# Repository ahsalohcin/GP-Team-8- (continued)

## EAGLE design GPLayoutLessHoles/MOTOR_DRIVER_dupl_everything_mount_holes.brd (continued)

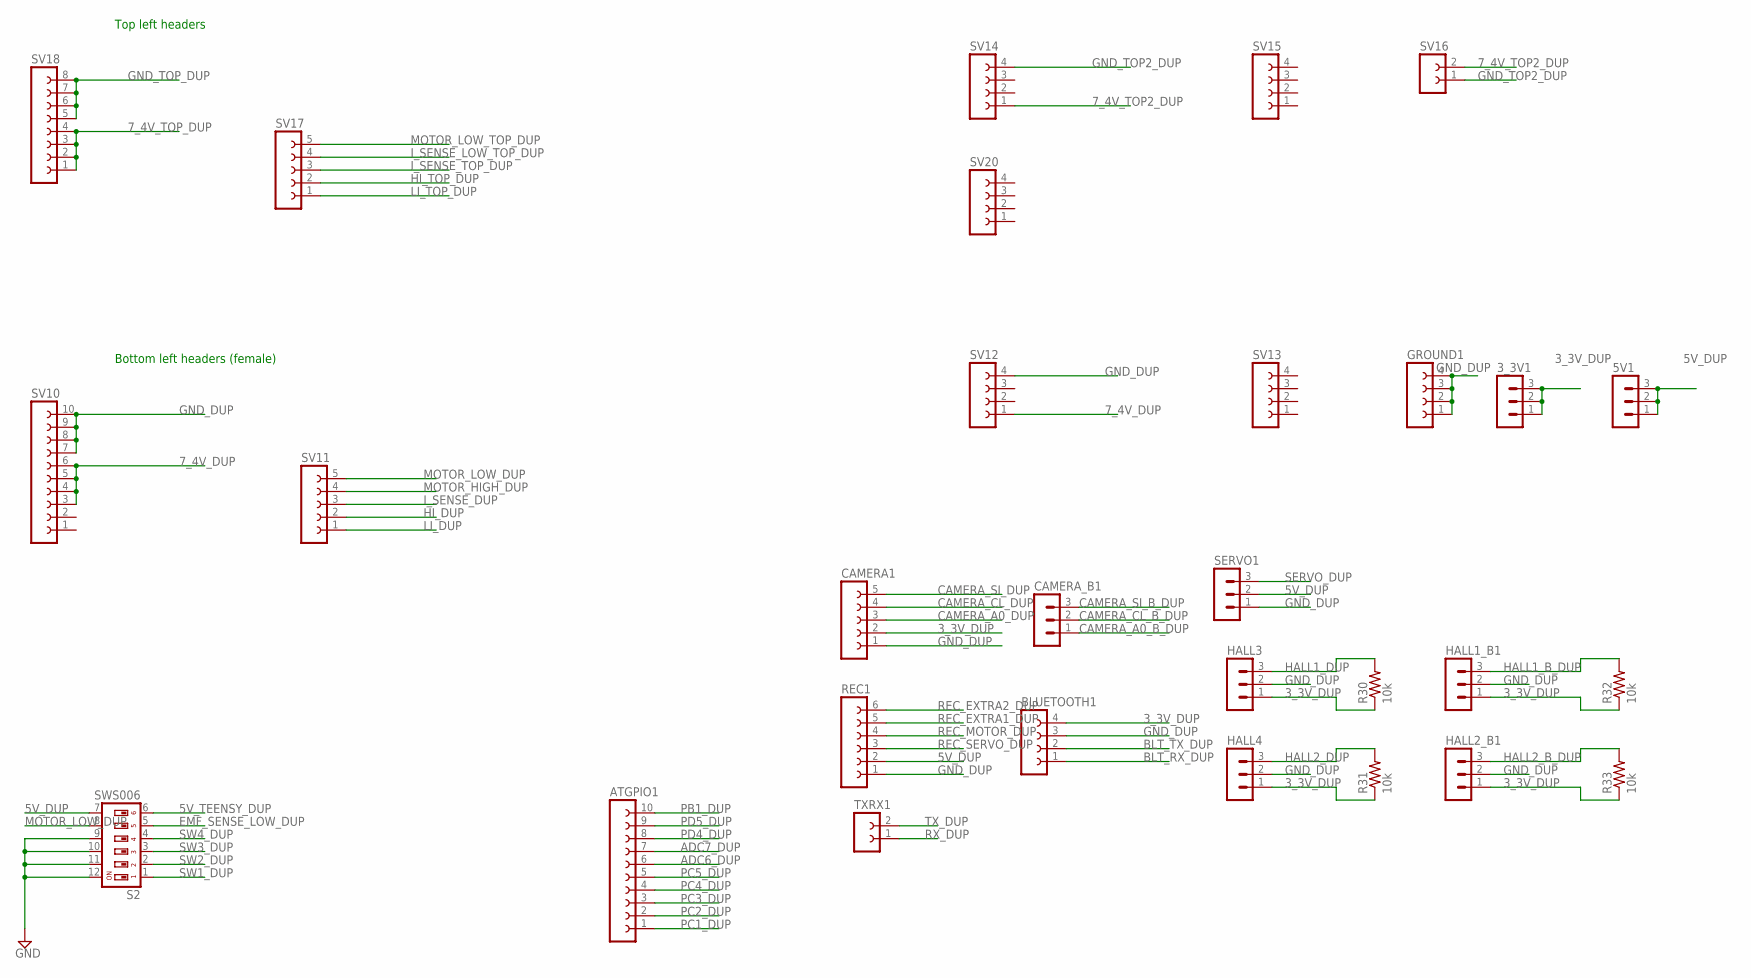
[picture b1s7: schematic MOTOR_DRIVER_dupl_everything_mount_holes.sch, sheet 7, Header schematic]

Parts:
3_3V1, 5V1: MA03-1
ATGPIO1: FE10-1; FE10
BLUETOOTH1: FE04-1; MANUFACTURER_PART_NUMBER HC-06
CAMERA1: FE05-1; MANUFACTURER_PART_NUMBER 28317; DIGIKEY_PART_NUMBER 28317-ND
CAMERA_B1: MA03-1; MANUFACTURER_PART_NUMBER 28317; DIGIKEY_PART_NUMBER 28317-ND
GROUND1: FE04-1
HALL1_B1, HALL2_B1, HALL3, HALL4: MA03-1; MANUFACTURER_PART_NUMBER US1881LUA-AAA-000-BU; DIGIKEY_PART_NUMBER US1881LUA-AAA-000-BU-ND
R30, R31, R32, R33: 10k; R0603
REC1: FE06-1; FE06
S2: SWS006; SMS-006; MANUFACTURER_PART_NUMBER 219-6MST; DIGIKEY_PART_NUMBER CT2196MST-ND
SERVO1: MA03-1; MANUFACTURER_PART_NUMBER TS-P12S
SV10: FE10-1; FE10
SV11, SV17: FE05-1
SV12, SV13, SV14, SV15, SV20: FE04-1
SV16: FE02-1
SV18: FE08-1; FE08
TXRX1: FE02-1

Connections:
3_3V_DUP: 3_3V1.1, 3_3V1.2, 3_3V1.3, BLUETOOTH1.4, CAMERA1.2, HALL1_B1.1, HALL2_B1.1, HALL3.1, HALL4.1, R30.1, R31.1, R32.1, R33.1; also elsewhere on the board
5V_DUP: 5V1.1, 5V1.2, 5V1.3, REC1.2, S2.7, SERVO1.2; also elsewhere on the board
5V_TEENSY_DUP: S2.6; also elsewhere on the board
7_4V_DUP: SV10.3, SV10.4, SV10.5, SV10.6, SV12.1; also elsewhere on the board
7_4V_TOP2_DUP: SV14.1, SV16.2; also elsewhere on the board
7_4V_TOP_DUP: SV18.1, SV18.2, SV18.3, SV18.4; also elsewhere on the board
ADC6_DUP: ATGPIO1.6; also elsewhere on the board
ADC7_DUP: ATGPIO1.7; also elsewhere on the board
BLT_RX_DUP: BLUETOOTH1.1; also elsewhere on the board
BLT_TX_DUP: BLUETOOTH1.2; also elsewhere on the board
CAMERA_A0_B_DUP: CAMERA_B1.1; also elsewhere on the board
CAMERA_A0_DUP: CAMERA1.3; also elsewhere on the board
CAMERA_CL_B_DUP: CAMERA_B1.2; also elsewhere on the board
CAMERA_CL_DUP: CAMERA1.4; also elsewhere on the board
CAMERA_SI_B_DUP: CAMERA_B1.3; also elsewhere on the board
CAMERA_SI_DUP: CAMERA1.5; also elsewhere on the board
EMF_SENSE_LOW_DUP: S2.5; also elsewhere on the board
GND_DUP: BLUETOOTH1.3, CAMERA1.1, GROUND1.1, GROUND1.2, GROUND1.3, GROUND1.4, HALL1_B1.2, HALL2_B1.2, HALL3.2, HALL4.2, REC1.1, S2.9, S2.10, S2.11, S2.12, SERVO1.1, SV10.7, SV10.8, SV10.9, SV10.10, SV12.4; also elsewhere on the board
GND_TOP2_DUP: SV14.4, SV16.1; also elsewhere on the board
GND_TOP_DUP: SV18.5, SV18.6, SV18.7, SV18.8; also elsewhere on the board
HALL1_B_DUP: HALL1_B1.3, R32.2; also elsewhere on the board
HALL1_DUP: HALL3.3, R30.2; also elsewhere on the board
HALL2_B_DUP: HALL2_B1.3, R33.2; also elsewhere on the board
HALL2_DUP: HALL4.3, R31.2; also elsewhere on the board
HI_DUP: SV11.2; also elsewhere on the board
HI_TOP_DUP: SV17.2; also elsewhere on the board
I_SENSE_DUP: SV11.3; also elsewhere on the board
I_SENSE_LOW_TOP_DUP: SV17.4; also elsewhere on the board
I_SENSE_TOP_DUP: SV17.3; also elsewhere on the board
LI_DUP: SV11.1; also elsewhere on the board
LI_TOP_DUP: SV17.1; also elsewhere on the board
MOTOR_HIGH_DUP: SV11.4; also elsewhere on the board
MOTOR_LOW_DUP: S2.8, SV11.5; also elsewhere on the board
MOTOR_LOW_TOP_DUP: SV17.5; also elsewhere on the board
PB1_DUP: ATGPIO1.10; also elsewhere on the board
PC1_DUP: ATGPIO1.1; also elsewhere on the board
PC2_DUP: ATGPIO1.2; also elsewhere on the board
PC3_DUP: ATGPIO1.3; also elsewhere on the board
PC4_DUP: ATGPIO1.4; also elsewhere on the board
PC5_DUP: ATGPIO1.5; also elsewhere on the board
PD4_DUP: ATGPIO1.8; also elsewhere on the board
PD5_DUP: ATGPIO1.9; also elsewhere on the board
REC_EXTRA1_DUP: REC1.5; also elsewhere on the board
REC_EXTRA2_DUP: REC1.6; also elsewhere on the board
REC_MOTOR_DUP: REC1.4; also elsewhere on the board
REC_SERVO_DUP: REC1.3; also elsewhere on the board
RX_DUP: TXRX1.1; also elsewhere on the board
SERVO_DUP: SERVO1.3; also elsewhere on the board
SW1_DUP: S2.1; also elsewhere on the board
SW2_DUP: S2.2; also elsewhere on the board
SW3_DUP: S2.3; also elsewhere on the board
SW4_DUP: S2.4; also elsewhere on the board
TX_DUP: TXRX1.2; also elsewhere on the board

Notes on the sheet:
Bottom left headers (female)
Top left headers

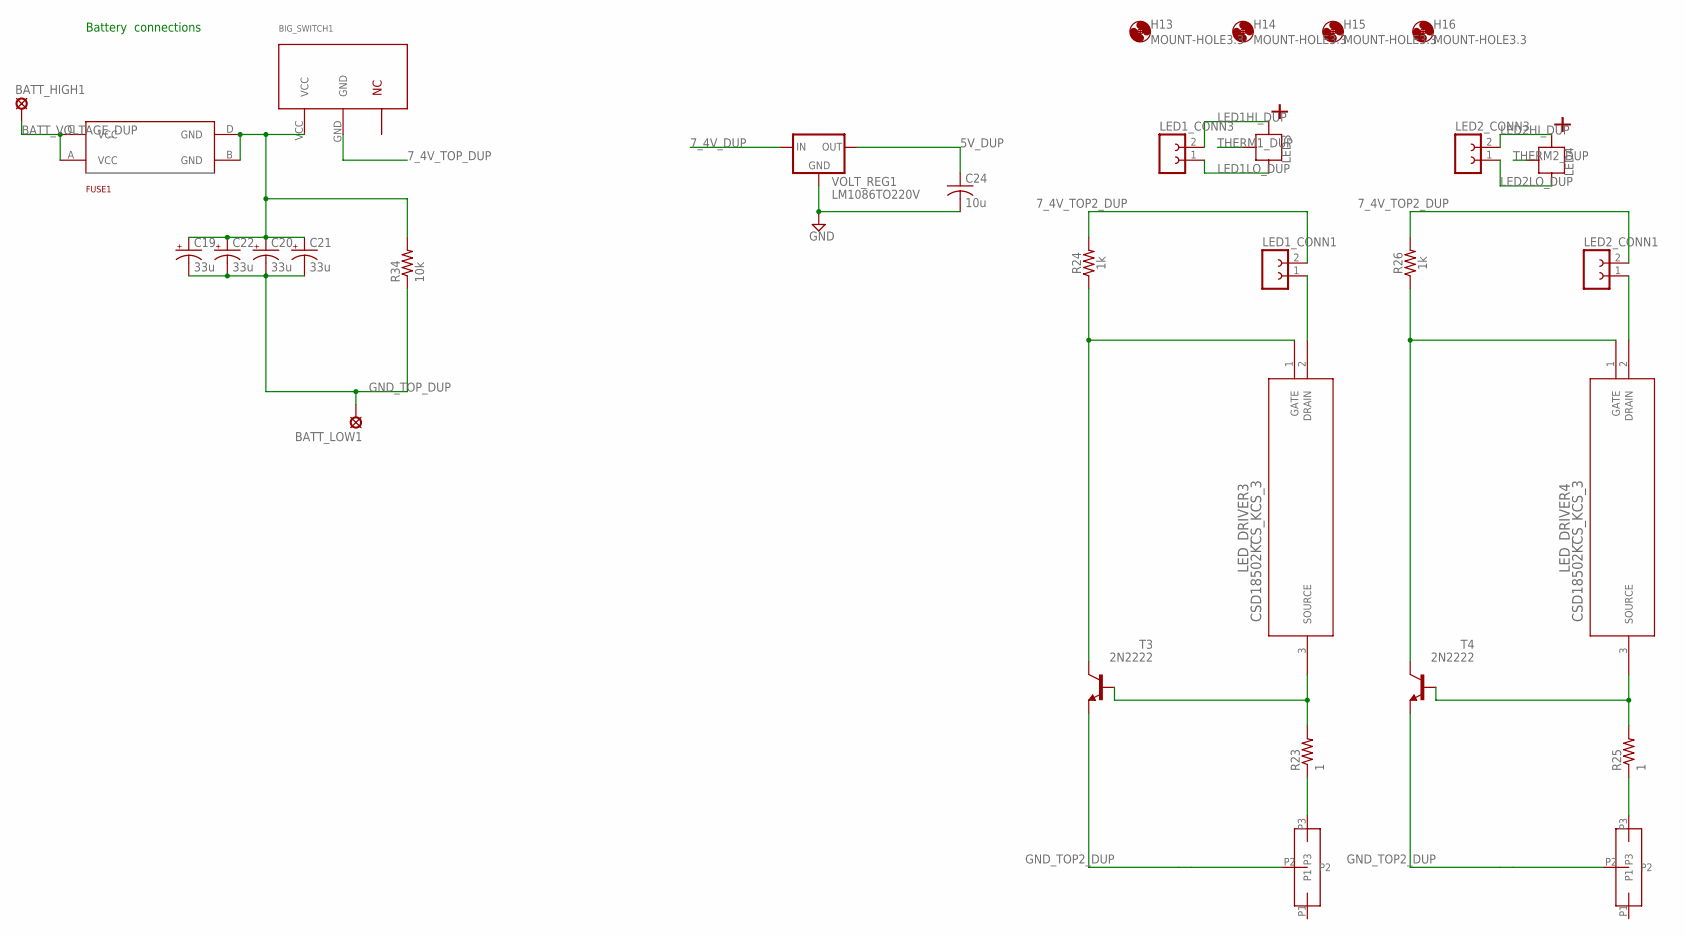
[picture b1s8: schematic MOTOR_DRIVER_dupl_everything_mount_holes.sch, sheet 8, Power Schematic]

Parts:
BATT_HIGH1: SE14
BATT_LOW1: SE14
BIG_SWITCH1: BIGSWITCH; MANUFACTURER_PART_NUMBER GRB238B801BR1; DIGIKEY_PART_NUMBER CW106-ND
C19, C20, C21, C22: 33u; 153CLV-1010
C24: 10u; C0805
FUSE1: FUSEHOLDER3588; MANUFACTURER_PART_NUMBER 0891010.NXS; DIGIKEY_PART_NUMBER F4989-ND
H13, H14, H15, H16: MOUNT-HOLE3.3; 3,3
LED1_CONN1, LED1_CONN3, LED2_CONN1, LED2_CONN3: FE02-1
LED3, LED4: CREE_XP; XP
LED_DRIVER3, LED_DRIVER4: CSD18502KCS_KCS_3; KCS3
R23, R25: 1; R2512
R24, R26: 1k; AXIAL-0.3
R34: 10k; R0603
T3, T4: 2N2222; TO18
U$14, U$15: POT
VOLT_REG1: LM1086TO220V; TO220S; MANUFACTURER_PART_NUMBER LM1086IT-5.0/NOPB; DIGIKEY_PART_NUMBER LM1086IT-5.0/NOPB-ND

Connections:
5V_DUP: C24.1, VOLT_REG1.2 (OUT); also elsewhere on the board
7_4V_DUP: VOLT_REG1.3 (IN); also elsewhere on the board
7_4V_TOP2_DUP: LED1_CONN1.2, LED2_CONN1.2, R24.P$2 (2), R26.P$2 (2); also elsewhere on the board
7_4V_TOP_DUP: BIG_SWITCH1.GND; also elsewhere on the board
BATT_VOLTAGE_DUP: BATT_HIGH1.MP, FUSE1.A (VCC), FUSE1.C (VCC)
GND_DUP: C24.2, VOLT_REG1.1 (GND); also elsewhere on the board
GND_TOP2_DUP: T3.1 (E), T4.1 (E), U$14.P2, U$15.P2; also elsewhere on the board
GND_TOP_DUP: BATT_LOW1.MP, C19.-, C20.-, C21.-, C22.-, R34.1; also elsewhere on the board
LED1HI_DUP: LED1_CONN3.2, LED3.POSITIVE, LED3.POSITIVE1 (POSITIVE)
LED1LO_DUP: LED1_CONN3.1, LED3.NEGATIVE, LED3.NEGATIVE1 (NEGATIVE)
LED2HI_DUP: LED2_CONN3.2, LED4.POSITIVE, LED4.POSITIVE1 (POSITIVE)
LED2LO_DUP: LED2_CONN3.1, LED4.NEGATIVE, LED4.NEGATIVE1 (NEGATIVE)
unnamed: BIG_SWITCH1.VCC, C19.+, C20.+, C21.+, C22.+, FUSE1.B (GND), FUSE1.D (GND), R34.2
unnamed: R23.1, U$14.P3
unnamed: LED_DRIVER3.3 (SOURCE), R23.2, T3.2 (B)
unnamed: LED_DRIVER3.1 (GATE), R24.P$1 (1), T3.3 (C)
unnamed: LED1_CONN1.1, LED_DRIVER3.2 (DRAIN)
unnamed: R25.1, U$15.P3
unnamed: LED_DRIVER4.3 (SOURCE), R25.2, T4.2 (B)
unnamed: LED_DRIVER4.1 (GATE), R26.P$1 (1), T4.3 (C)
unnamed: LED2_CONN1.1, LED_DRIVER4.2 (DRAIN)
THERM1_DUP: LED3.THERMAL
THERM2_DUP: LED4.THERMAL

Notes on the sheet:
Battery connections

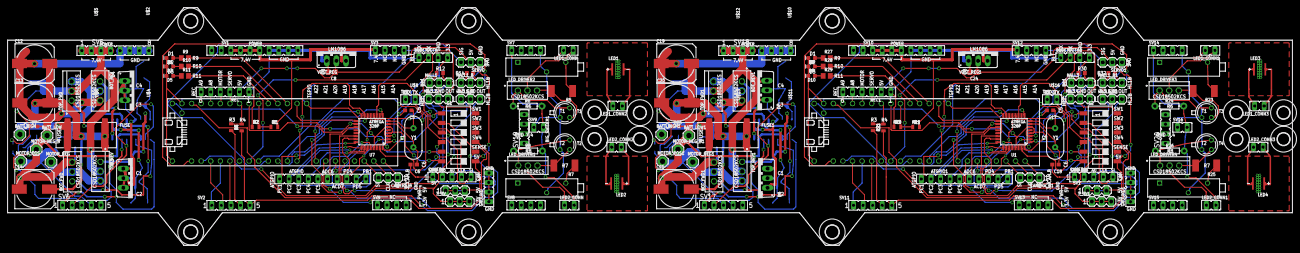
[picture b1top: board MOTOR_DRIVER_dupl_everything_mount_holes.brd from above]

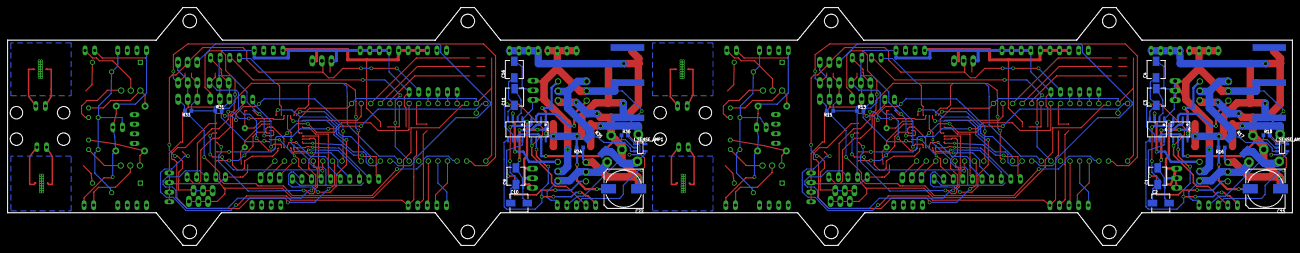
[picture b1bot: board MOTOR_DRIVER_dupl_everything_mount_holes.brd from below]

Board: 2 copper layers, 340.4 x 63.0 mm, 206 parts (26 on the bottom side), 180 nets.

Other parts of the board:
U$8, U$16: HEATSINK

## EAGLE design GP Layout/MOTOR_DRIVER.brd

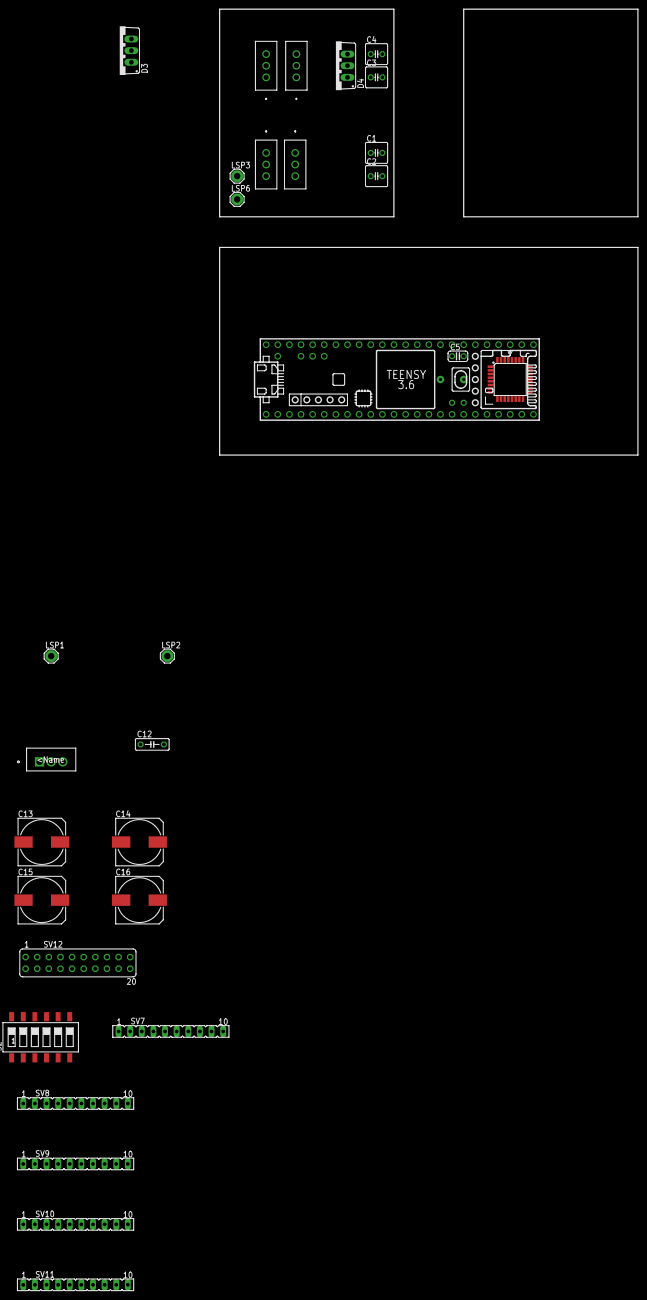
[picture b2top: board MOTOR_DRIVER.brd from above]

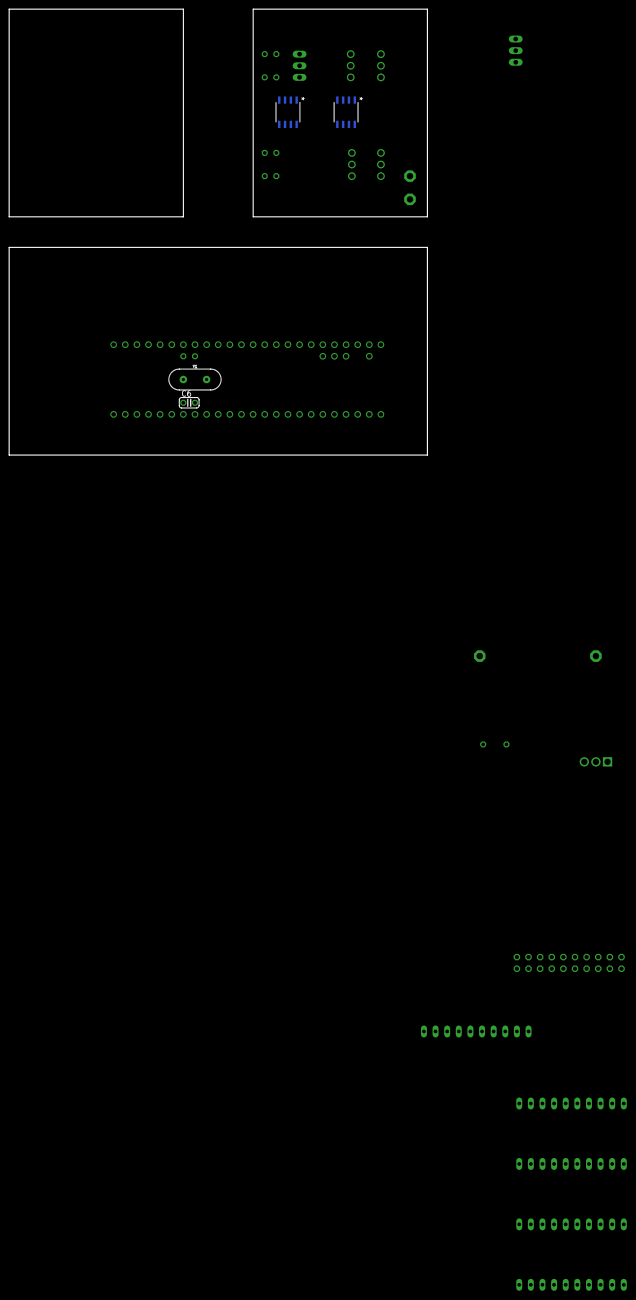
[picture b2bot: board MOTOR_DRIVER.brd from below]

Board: 2 copper layers, 91.4 x 97.5 mm, 34 parts (4 on the bottom side), 43 nets, no tracks yet.

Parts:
C1, C2, C3, C4: 10uF; C025-050X050
C5, C6: 18 pF; C025-024X044
C12: 10uF; C050-025X075
C13, C14, C15, C16: 153CLV-1010
D3, D4: BYV32; TO220ABS
LSP1, LSP2, LSP3, LSP6: SE14
S2: SWS006; SMS-006
SV7, SV8, SV9, SV10, SV11: FE10
SV12: FE10-2
TOP_FWD: CSD18502KCS_KCS_3; KCS3
U2, U4, U5: CSD18502KCS_KCS_3; KCS3
U3, U6: MIC4604YM; SOIC-8_M
U7: ATMEGA328P_TQFP; TQFP32-08
U$1: TEENSY_3.5/3.6_BASIC
U$2: LM1086IT-5.0/NOPB; T03B
Y1: 16MHz; HC49US

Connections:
3_3V: SV12.9, U$1.3V3_LO
5V: C12.1, S2.7, SV12.7, SV12.18, U7.4, U7.6, U7.18, U7.29, U$2.2
5V_TEENSY: S2.6, U$1.VIN
7_4V: SV7.1, U$2.3
7_4V_TOP: D3.A1, D3.A2, D4.A1, D4.A2, LSP1.MP, SV10.1, TOP_FWD.2, U3.1, U4.2, U6.1
BLT_RX: SV12.1, U$1.7
BLT_TX: SV12.3, U$1.8
CAMERA_A0: SV12.17, U7.23
CAMERA_CLK: SV12.13, U7.12
CAMERA_SI: SV12.15, U7.11
GND: C5.2, C6.2, C12.2, S2.8, S2.9, S2.10, S2.11, S2.12, SV12.5, SV12.11, SV12.12, SV12.14, U7.3, U7.5, U7.21, U$1.AGND, U$1.GND, U$1.GND2, U$2.1
GND_TOP: C16.-, LSP2.MP, SV10.10, U2.3, U3.7, U5.3, U6.7
HALL: SV12.16, U7.32
HI: SV8.1, U$1.3/CANTX
HI_TOP: SV11.1, U3.5, U6.6
LI: SV8.2, U$1.4/CANRX
LI_TOP: SV11.2, U3.6, U6.5
unnamed: LSP3.MP, TOP_FWD.3, U2.2
unnamed: U2.1, U3.8
unnamed: TOP_FWD.1, U3.3
unnamed: C1.1, C2.1, U3.4
unnamed: C1.2, C2.2, D3.C, U3.2
unnamed: C6.1, U7.7, Y1.1
unnamed: C5.1, U7.8, Y1.2
unnamed: LSP6.MP, U4.3, U5.2
unnamed: U5.1, U6.8
unnamed: U4.1, U6.3
unnamed: C3.1, C4.1, U6.4
unnamed: C3.2, C4.2, D4.C, U6.2
unnamed: U7.14, U$1.10/CS
unnamed: U7.15, U$1.12/MISO
unnamed: U7.17, U$1.13/SCK
unnamed: U7.16, U$1.11/MOSI
unnamed: C15.-, C16.+
unnamed: C14.-, C15.+
unnamed: C13.-, C14.+
RX: SV12.20, U7.30
SW1: S2.1, U$1.24
SW2: S2.2, U$1.25
SW3: S2.3, U$1.26
SW4: S2.4, U$1.27
SW5: S2.5, U$1.28
TX: SV12.19, U7.31

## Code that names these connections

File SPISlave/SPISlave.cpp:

#include <Arduino.h>
#include "SPISlave.h"

volatile int cntr;
byte cmd = 0;
uint8_t addr;
byte spi_state = 0;
float * datap;
byte * settingsp;
volatile byte flt_cnt;

union{
  float data_float;
  byte data_byte[sizeof(float)];
} data;

void init_SPI(void)
{
  //DDRB &= ~(1<<PB1) & ~(1<<PB2) & ~(1<<PB6) & ~(1<<PB7);
  DDRB &= ~((1<<PB5)|(1<<PB3)|(1<<PB2));   // SCK, MOSI and SS as inputs
  DDRB |= (1<<PB4);                    // MISO as output
  SPCR &= ~(1<<MSTR);                // Set as slave
  SPCR |=(1<<SPR0);
  //SPCR |= (1<<SPR1);       
  //SPSR |= (1<<SPI2X);
  SPCR |= (1<<SPE);                  // Enable SPI
  SPCR |= (1<<SPIE);           // Enable Interrupt
  spi_state = 0;
  cmd = 0;
  SPDR = 0;
}

void pointToData(float * data_point, byte * settings){
  datap = data_point;
  settingsp = settings;
}

void resetSPI(){
  if (digitalRead(SS) == HIGH){
    cmd = 0;
    spi_state = 0;
    flt_cnt = 0;
    byte stat = SPSR;
  }
}

ISR (SPI_STC_vect)
{
  if (spi_state == 163){
    spi_state = 0;
  }
  byte c = SPDR;
  //Serial.println(spi_state);
 switch (spi_state){
    case 0:
      cmd = c;
      spi_state = 1;
      break;
    case 1:
      addr = c;
      if (cmd == READ_CMD){
        if (addr == 0){
          data.data_float = *datap;
          while(!(SPSR & (1<<SPIF)));
          SPDR = data.data_byte[0];
          //Serial.println(data.data_byte[0], HEX);
          flt_cnt = 1;
        }else{
          while(!(SPSR & (1<<SPIF)));
          SPDR = *(settingsp + addr);
          cmd = 0;
          spi_state = 0;
          flt_cnt = 0;
          break;
        }
      }
      spi_state = 2;
      break;
    case 2:
      if (cmd == READ_CMD){
        if (addr != 0){
          spi_state = 0; 
          break;
        }
        if (flt_cnt < FLOAT_SIZE){
          //while(!(SPSR & (1<<SPIF)));
          SPDR = data.data_byte[flt_cnt++];
          //Serial.println(data.data_byte[flt_cnt-1], HEX);
        }
      }else if (cmd == WRITE_CMD){
        *(settingsp+addr) = c;
        cmd = 0;
        spi_state = 0;
        flt_cnt = 0;
        break;
      }
      break;
    default:
      spi_state = 0;
      break;
  }
}

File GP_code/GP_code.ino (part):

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  void getPot();

  // transmitter and motor driver
  int REC_MOTOR = 15; // pin to read signals from reciever
  int throttleValue;
  int topDutyCycle = 256; // = 100%
  int buffTx = 100; // buffer for tx input . full range of tx input is 1160 to 1830
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
// SERVO
//************************************************************************
  int REC_SERVO = 18;
  int SERVO = 20;
  
  int servoValueMicro; //1000-2000 for full range. is actually less because of the physical stops 
  int servoMidMicro = 1455; // 2/18 test: min 1140, max 1770 before running into mechanical stops
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  
// DIAGNOSTICS
//************************************************************************
  double BATT_VOLTAGE_SENSE = 17; //pin number;
  double battVoltSenseVal;
  double battVoltVal;
  double battConst = 2.728; // (R2+R1)/R1; R1 = 2.8k, R2 = 1.62k 
  double battPeriod = 1000; 
  double battPrevTime = 0;

  double EMF_SENSE_HIGH = 19;
  double emfSenseHigh = 0;
  double EMF_SENSE_LOW = 18;
  double emfSenseLow = 0;
  double emfConst = 3.0174; // (R3+R4)/R4; R3 = 2.32k, R4 = 1.15k
  double emfHigh; // emfHighV = (emfSenseHighVal - emfSenseLowVal)*emfConst;
  double emf; //emf = emfHigh-emfSenseLow

  double I_SENSE = 5;
  double iSenseV;
  double iCalc;
  double iConst = 2.5; // 5k /(RS*RL) RS = .02 RL = 100k. unreliable with RL = 100k? RL = 10k better for ADC
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    //analogWriteFrequency(LI, 9800);
    
  //for transmitter throttle
    pinMode(REC_MOTOR,INPUT);
  
  //camera stuff
    pinMode(pinSI,OUTPUT);
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    pinMode(pinAO, INPUT);
  
  //from transmitter to control the servo
    pinMode(REC_SERVO,INPUT);
    myServo.attach(SERVO);

  //speed sensing
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    attachInterrupt(digitalPinToInterrupt(hallPin_R), magnet_detect_R, RISING); //set up interrupt function. should work on any teensy pin.

  // diagnostics
    pinMode(BATT_VOLTAGE_SENSE,INPUT);
    
    pinMode(EMF_SENSE_HIGH, INPUT);
    pinMode(EMF_SENSE_LOW,INPUT);

    pinMode(I_SENSE, INPUT);
    
  //indicator LED that program is running
    pinMode(13, OUTPUT);
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
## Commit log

2016-10-25 added folder for circuit simulations.
2016-10-25 tried to simulate a DC motor and switching characteristics
2017-01-22 added last year's code that Nick shared with me
2017-01-22 demo for motor, transmitter, camera,servo
2017-01-22 teensy updated
2017-01-22 Added bluetooth code
2017-01-29 Added function average elements of an array
2017-01-29 Added diff function
2017-01-29 added .gitignore
2017-01-29 moved serialprint outside of getline
2017-01-29 Added center fucntion
2017-02-04 made camera mount
2017-02-05 description
    Organized code: made more functions and comments. Changed some data types in filtering functions. Added hall effect stuff
2017-02-05 organized, added functions, changed some variable types, added hall effect stuff
2017-02-05 Added layout files
    Layout files are in GPLayout folder
2017-02-05 Added updated layout files
2017-02-05 Updated all schematic sheets
2017-02-06 changed Servo.write to Servo.writemicroseconds
2017-02-11 Multilevel design
2017-02-12 component placement
2017-02-12 adding HES mount and some old files
2017-02-12 made footprint of fuse holder
2017-02-12 2 level design - incomplete
2017-02-12 Changed to two schematic sheets
2017-02-12 Back to 4 schematic sheets
2017-02-12 Actual 4 schematic sheet update
2017-02-15 switch and fuse
2017-02-15 modified power schematic, added battery sense, named motor terminals
2017-02-15 added some heatsink outlines
2017-02-17 modified footprint for MOS to have name and indicate orientation
2017-02-18 Changed battery sense resistances
    Input impedance might be too high for the Teensy ADC
2017-02-18 Updated servo configuratons (servo middle and range)
2017-02-18 deleted extra steering command
2017-02-19 added motor inputs for full bridge
2017-02-19 fixed LI2 and HI2 errors
2017-02-19 added backup pins on Teensy for camera and HES
2017-02-20 t :wq # Explicit paths specified without -i or -o; assuming --only paths...
2017-02-20 messed up some git command, made new folder. major changes to connectors. may be missing lbr files for some parts. work in progress.
2017-02-24 checking that its updated
2017-02-25 added gpio, modified layout
2017-02-25 ISCP connectors
2017-02-26 added led driver, indicator leds, etc
2017-02-26 double check
2017-02-26 batt voltage connection fixed
2017-02-26 moved dip switch
2017-02-26 added actual LEDs
2017-02-26 added some resistors
2017-02-26 added some resistors, atmega gpio, placed them
2017-02-26 modified placement
2017-02-26 modified placement of header pins
2017-02-27 new folder with same schematic and board as last version of GP Layout 2. This folder contains all libraries used in that design as of 2/26. Use this folder from now on
2017-03-05 Upper board layout
2017-03-05 Added component attributes
    Added manufacturer, part number, and price to part attributes.
2017-03-05 Fixed a couple top wires on gate driver chip and gnd
2017-03-05 Added more wires to top board
2017-03-05 Fixed silkscreen for bottom layer
2017-03-06 Added current sense, needed to change a few pins on upper left. Check routing again. Changed rec header to female
2017-03-06 changed voltage regulator cap
2017-03-07 Updated top routing to include current sense resistor at 135 degree angle.
    4pcb should be checked to see if they can make the pads for the angled
    component
2017-03-07 Fixed errors on top board and moved current sense amp to top
2017-03-08 Fixed missing wire
2017-03-08 Fixed missing motor_high_top pin, now I_SENSE_LOW_TOP
2017-03-08 Routed lower board and combined all boards
    typical_4pcb.dru lists design errors for the width of the traces, but
    the file is outdated and trace widths correspond with 4pcb's website
2017-03-08 added several resistor values
2017-03-08 made overall dimensions smaller, moved I_SENSE and added back a GPIO. made an attempt at a gerber file
2017-03-09 Added silkscreen for most headers
2017-03-09 Added more silkscreen
2017-03-12 most recent gerbers
2017-03-12 code for camera testing
2017-03-12 gathered sample camera data; initial MATLAB visualization code
2017-03-12 added thermal things for LEDs
2017-03-12 fixed thermals
2017-03-12 Changed drill hole sizes
2017-03-13 changed some drill sizes to .8 instead of .6. fixed some clearance issues with LED
2017-03-13 larger pad for LEDs
2017-03-14 added folder with version with less holes
2017-03-16 reduced GPIOs on teensy and started on atmega
2017-03-17 more edits
2017-03-17 more edits. will try rerouting top after this one
2017-03-17 undid rerouting
2017-03-17 new caps rerouted a lot, thinner wires, wider clearances
2017-03-17 re did tstop and bstop
2017-03-17 several duplicated versions. duplic_everything is the one to use
2017-03-17 gerbers
2017-03-18 added version with mounting holes
2017-03-18 cleaned up dimensions neater
2017-03-20 added more mounting holes and headers, renamed switches. ordered this 3/20
2017-04-11 some modified board and new driving code for single thread and half or full bridge
2017-04-11 added diagnostics functions: batt voltage, i_sense, and emf sense. changed a few variable names
2017-04-11 add prototype speed feedback code
2017-04-13 fixed pin numbers for driving and steering. Increased buffer size, shrank max speed. changed led status lights
2017-04-13 old camera mount parts
2017-04-15 changed name of sketch
2017-04-15 started GP_AVR code, does not compile
2017-04-16 new HES mounts 20 mill error
2017-04-16 also a 3 mill error version
2017-04-16 added rudimentary state flow: pauses program and turns off motor when pause signal is high
2017-04-16 added speed sensing, more state flow. pauses when battery low or going too fast
2017-04-22 Added bluetooth communcation code
2017-04-22 Fixed conflict in stateCheck()
2017-04-22 Added uninterrupt copy code and sent speed telemetry
2017-04-22 Tested bluetooth pause functionality
2017-04-22 some speed feedback
2017-04-22 added kiSpeed, vErrorTotal and demostrated PI control speed
2017-04-26 Bidirectional SPI communication
    Features: CRC8, float transfer, register transfer, testbench
2017-04-26 Changes to the SPI testbench to reflect performance
2017-04-26 changed state flow and drive modes. some unknown issue with Tx pausing
2017-04-26 Added multithreaded folder and SPI
2017-04-26 modified CL speed control and off mode
2017-04-30 telemetry for matlab. sends data every .1 sec
2017-04-30 modified for matlab telemetry. current issues are still with reading negative speed.
2017-05-03 made header files
2017-05-03 finished header files
2017-05-03 added lots of comments, drive modes, and backup motor modes
2017-05-04 more organization, was testing steer angles. Added some pure pursuit
2017-05-05 fixed Tx state flow a little
2017-05-05 added pure pursuit and some steering stateflow
2017-05-05 added arduino code that uses the arduino library
2017-05-05 changed limits for motor value
2017-05-05 Changes to SPI
2017-05-05 added more pure pursuit
2017-05-06 Finally functioning SPI!
2017-05-06 arduino code
2017-05-06 lots of code changes
2017-05-06 minor changes
2017-05-06 working pretty well with averaging 3 and 4000 us looptime
2017-05-06 added some stucture for time averaging
2017-05-06 Changed LED indicators to low battery voltage and state==play
2017-05-06 added curavature calculation
2017-05-06 added condition when camera loses line
2017-05-07 added untested curvature calcs and display. moved xError Calc and curvature calc
2017-05-07 new thread to use
2017-05-07 added mode for slowing down based on curvature. one thats a linear function, and one that drops a certain number if curvature is too high
2017-05-07 added line losing detection and reaction. works on table, untested on track
2017-05-07 added kP dependence on speed. untested
2017-05-07 syntax fixed
2017-05-07 working well at 6 ft/sec. soft start bad. line fault detection unverified. slow on turn or kp on speed untested
2017-05-07 good soft start and reverse half
2017-05-07 start dropping speed on turns, threshold method
2017-05-07 working well, proportional speed drop. looptime 5 ms. 8 ft sec , drop by 2. averaging 5 for camera
2017-05-07 Modified kSteering as a function of speed.
2017-05-07 Revert "Modified kSteering as a function of speed."
    This reverts commit 778f44da520788cfeae3ac430b496e4d0573a8e8.
2017-05-07 median filtered, modified battery warnings. changed line fault conditions, no longer working
2017-05-07 improved fault detection
2017-05-07 goes left
2017-05-07 goes left #2
2017-05-09 code from GP competition. added a readme
2017-05-09 removed extra unused functions
2017-05-09 added untested kD for improving steering
2017-05-09 added mode to double speed time resolution. should trigger on both rising and falling edges, or 6 times a rotation
2017-05-10 changed L and R to 1 and 2. Also added code to detect the direction of wheel spinning. Requires another HES in same orientation
2017-05-10 signed wheel speed works
2017-05-10 added pseudocode for track memory. Two different methods
2018-12-03 Create none
